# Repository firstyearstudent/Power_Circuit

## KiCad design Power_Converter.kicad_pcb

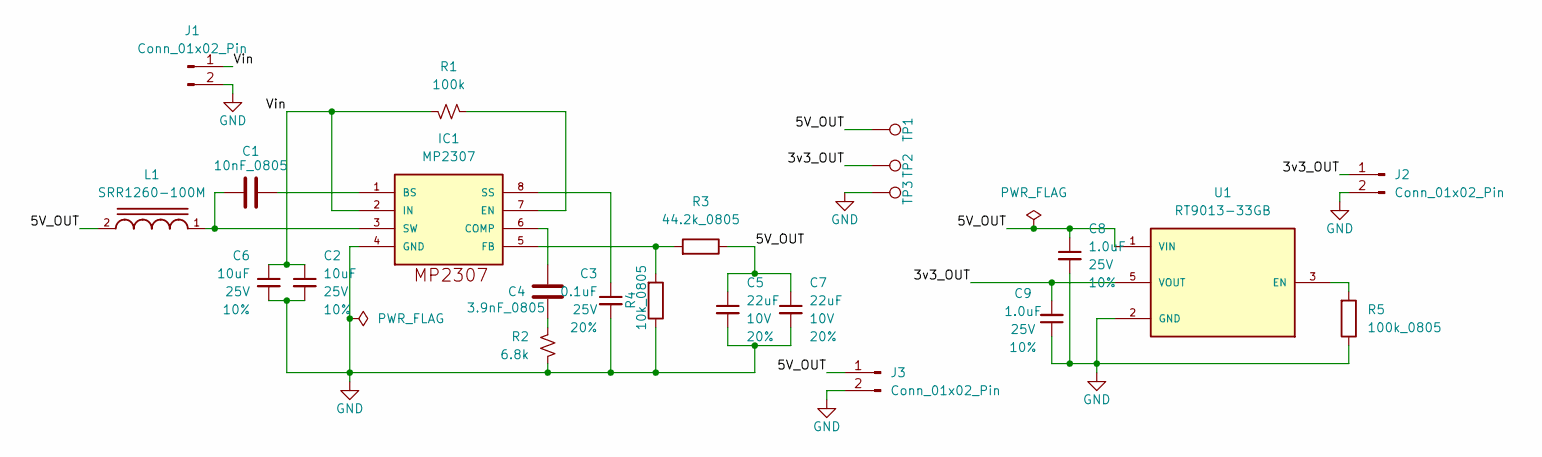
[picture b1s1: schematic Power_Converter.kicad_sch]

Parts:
C1: 10nF_0805; C_0805_2012Metric
C2, C6: 10uF; C_0805_2012Metric; Voltage 25V; Tolerance 10%
C3: 0.1uF; C_0603_1608Metric; Voltage 25V; Tolerance 20%
C4: 3.9nF_0805; C_0805_2012Metric
C5, C7: 22uF; C_0805_2012Metric; Voltage 10V; Tolerance 20%
C8, C9: 1.0uF; C_0805_2012Metric; Voltage 25V; Tolerance 10%
IC1: MP2307; SO8-TH
J1, J2, J3: Conn_01x02_Pin; PinHeader_1x02_P2.54mm_Vertical
L1: SRR1260-100M; INDP125125X600N
R1: 100k; R_0603_1608Metric
R2: 6.8k; R_0603_1608Metric
R3: 44.2k_0805; R_0805_2012Metric
R4: 10k_0805; R_0805_2012Metric
R5: 100k_0805; R_0805_2012Metric
TP1, TP2, TP3: 0.75mm; TestPoint-0.75mm
U1: RT9013-33GB; SOT94P279X129-5N; PARTREV Aprill 2011

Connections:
/3v3_OUT: C9.2, J2.1, TP2.1 (1_1), U1.5 (VOUT)
/5V_OUT: C5.1, C7.1, C8.1, J3.1, L1.2, R3.2, TP1.1 (1_1), U1.1 (VIN)
/Vin: C2.1, C6.1, IC1.2 (IN), J1.1, R1.1
GND: C2.2, C3.2, C5.2, C6.2, C7.2, C8.2, C9.1, IC1.4 (GND), J1.2, J2.2, J3.2, R2.1, R4.2, R5.2, TP3.1 (1_1), U1.2 (GND)
unnamed: C4.2, R2.2
unnamed: C1.2, IC1.1 (BS)
unnamed: C4.1, IC1.6 (COMP)
unnamed: IC1.7 (EN), R1.2
unnamed: IC1.5 (FB), R3.1, R4.1
unnamed: C3.1, IC1.8 (SS)
unnamed: C1.1, IC1.3 (SW), L1.1
unnamed: R5.1, U1.3 (EN)

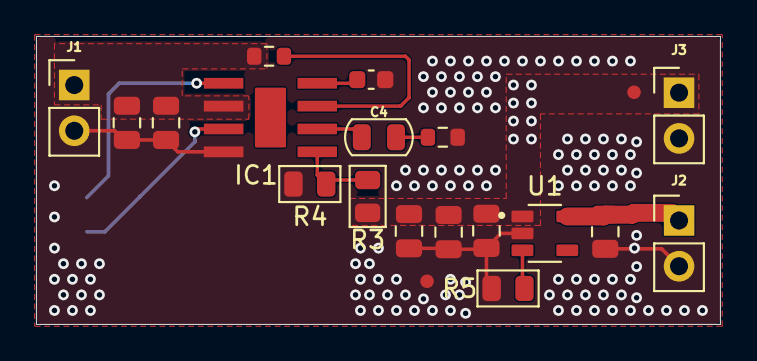
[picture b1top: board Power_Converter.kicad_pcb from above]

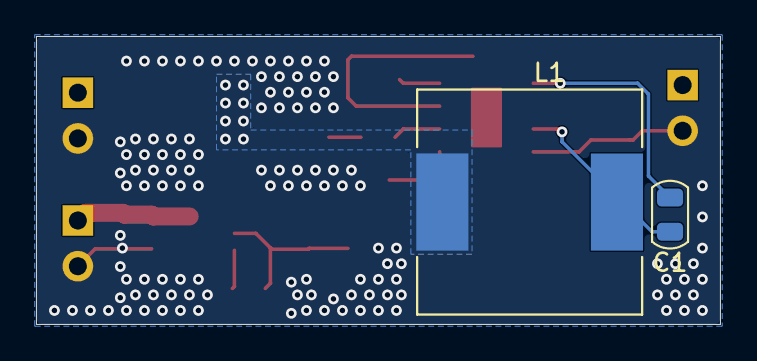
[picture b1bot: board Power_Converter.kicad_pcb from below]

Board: 2 copper layers, 38.0 x 16.0 mm, 23 parts (2 on the bottom side), 12 nets.
